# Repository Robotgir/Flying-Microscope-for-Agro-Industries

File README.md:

# Flying Microscope (SPECTORS)
This repo contains hardware and software details for the spore collector device which can be remotely controlled via Spectors Cockpit. Live image can be acessed on Spectors Cockpit.
## Code 
contains main script file named sporecollector1.py and its dependensies
### noteson_code.docx 
few details about the input variables in sporecollector1.py

## Docs 
contais system chart hand sketch  (Digital version yet to come)
### SystemChart.png coming soon
//

## Hardware
### camera_sieveholderassembly
contains priliminary and current designs for the spore collector device
### PCB (RPI HAT)
 contains Eagle board and schematic files for the PCB design
### productdata sheets
contain all the hardware components datasheets
#### PCB_connection_notes.docx 
contains details of how to setup the PCB AS Rpi-hat, connections with other components.

## Spore collection images
Images obtained from the measurment process

## PCB-Rpi-hat

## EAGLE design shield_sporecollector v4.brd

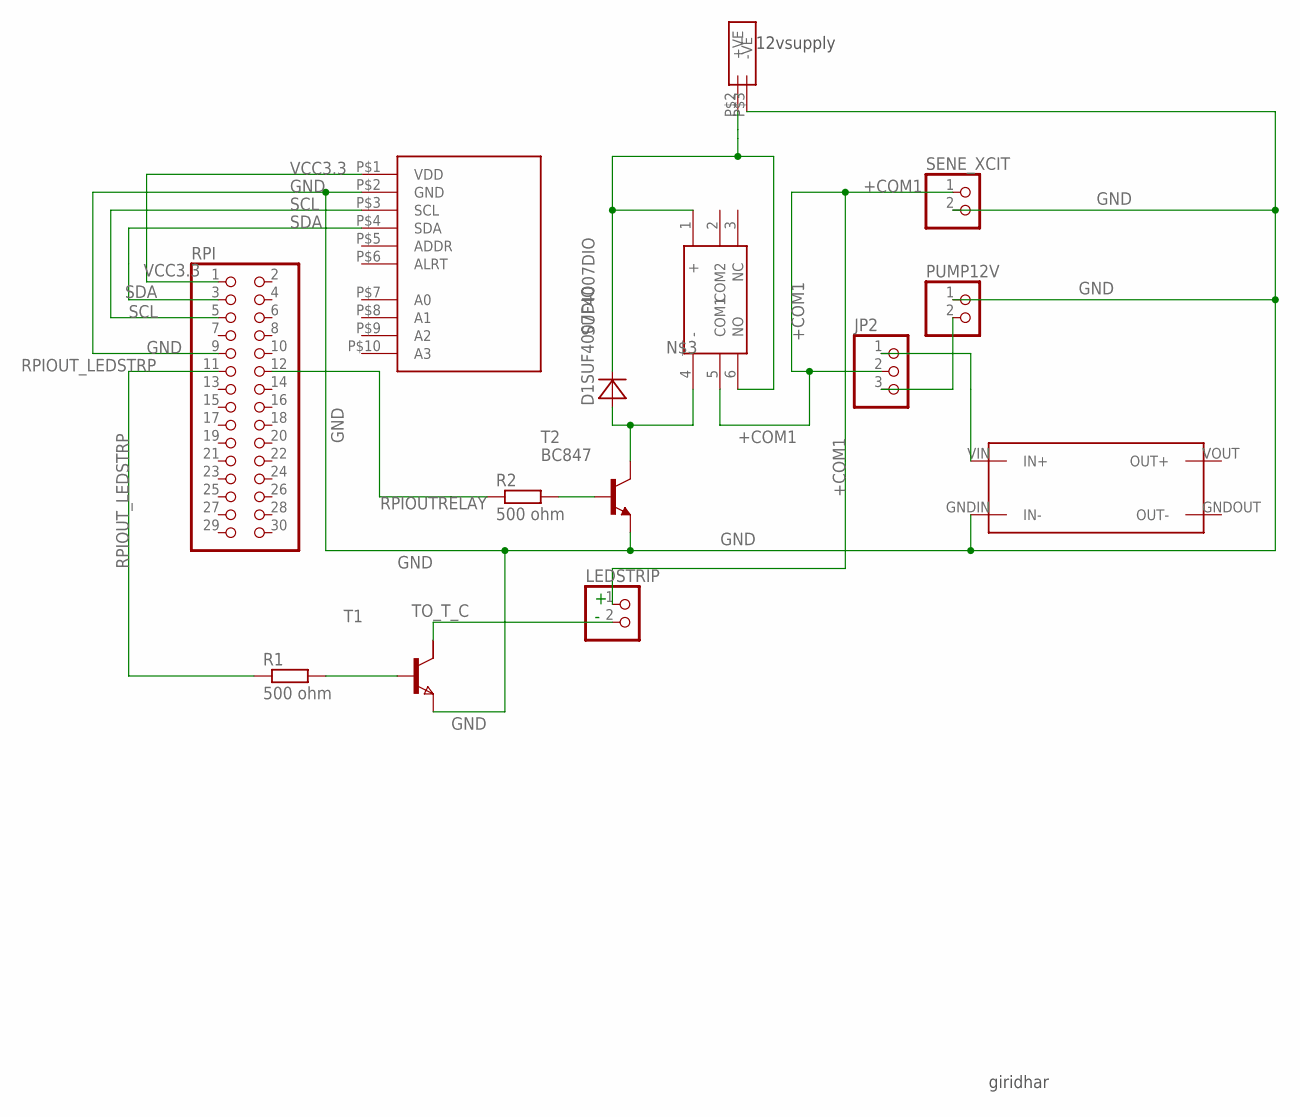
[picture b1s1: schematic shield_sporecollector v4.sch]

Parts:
BUCHSE12VINPUT: BUCHSE9.8X14.6
D1SUF4007DIO: SUF4007DIO; SUF4007
JP2: PINHD-1X3; 1X03
LEDSTRIP: PINHD-1X2; 1X02
PUMP12V: PINHD-1X2; 1X02
R1, R2: 500 ohm; R0603
RPI: PINHD-2X15; 2X15
SENE_XCIT: PINHD-1X2; 1X02
STEPUP12TO24V: 24VSTEPUPPOLOLUSMDSMD; STEP-UP24VSMD
T1: NPNSOT223; SOT223
T2: BC847; SOT23
U$3: ADC-4CH-ADS1115/WITHOUTHOLESADC-ADS1115WITHOUTHOL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; ADC-4CH-ADS1115/WITHOUTHOLES
U$4: G6B-2114POMRON; G6B-2114P

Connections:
+COM1: JP2.2, LEDSTRIP.1, SENE_XCIT.1, U$4.5 (COM1)
GND: BUCHSE12VINPUT.P$3 (-VE), PUMP12V.1, RPI.9, SENE_XCIT.2, STEPUP12TO24V.GNDIN (IN-), T1.3 (E), T2.2 (E), U$3.P$2 (GND)
unnamed: R2.2, T2.1 (B)
unnamed: R1.2, T1.1 (B)
unnamed: BUCHSE12VINPUT.P$2 (+VE), D1SUF4007DIO.C, U$4.1 (+), U$4.6 (NO)
unnamed: JP2.3, PUMP12V.2
unnamed: JP2.1, STEPUP12TO24V.VIN (IN+)
RELAY_T3_-_COIL: D1SUF4007DIO.A, T2.3 (C), U$4.4 (-)
RPIOUTRELAY: R2.1, RPI.12
RPIOUT_LEDSTRP: R1.1, RPI.11
SCL: RPI.5, U$3.P$3 (SCL)
SDA: RPI.3, U$3.P$4 (SDA)
TO_T_C: LEDSTRIP.2, T1.2 (C1)
VCC3.3: RPI.1, U$3.P$1 (VDD)

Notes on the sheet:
giridhar
12vsupply

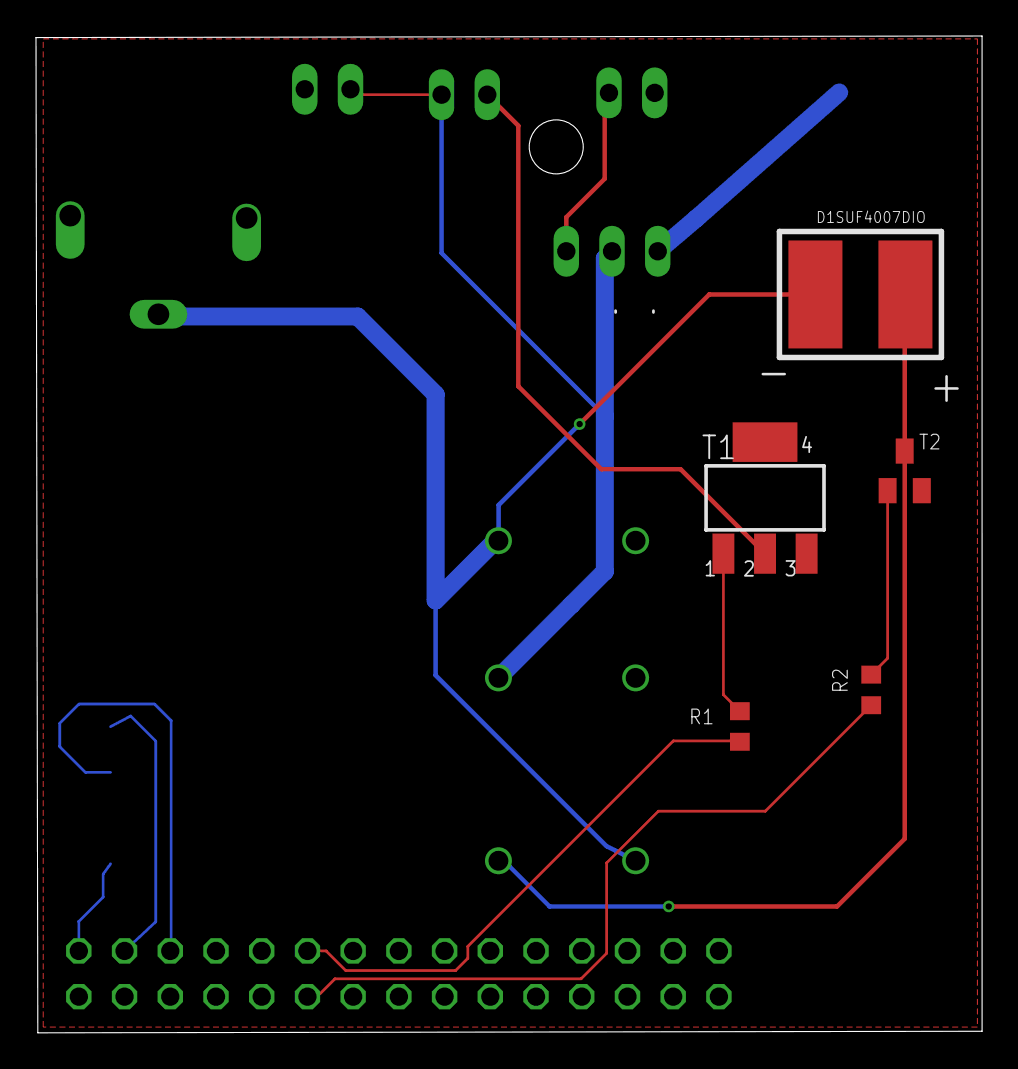
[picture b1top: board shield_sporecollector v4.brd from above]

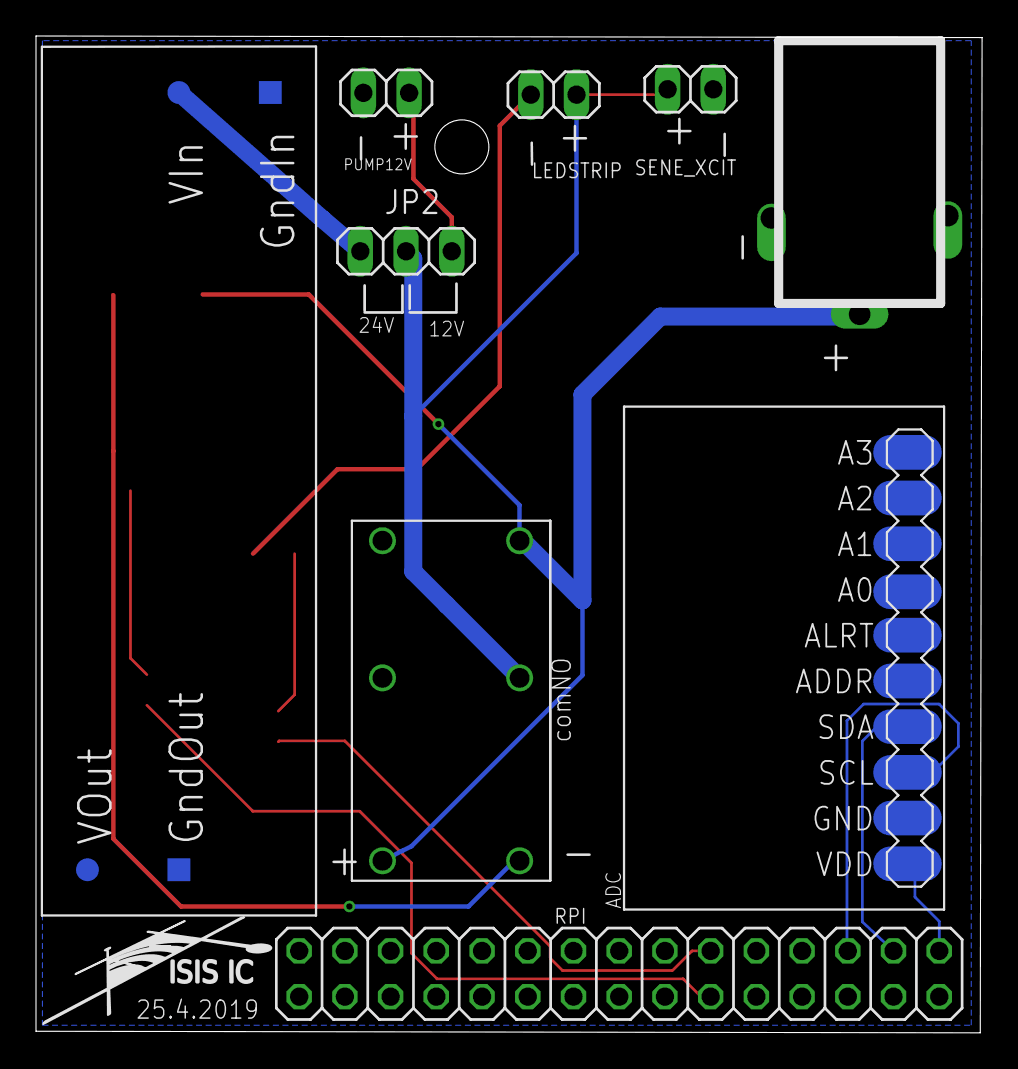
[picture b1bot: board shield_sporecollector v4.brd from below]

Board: 2 copper layers, 52.6 x 55.4 mm, 14 parts (9 on the bottom side), 14 nets.

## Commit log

2019-12-01 first update
2019-12-02 removed reports
2020-01-09 mage file_uploader to cloud
    image file_uploader to cloud
2020-01-10 info
2020-01-22 diffupload_method
2020-02-21 added python/bash scripts to upload the image and start/stop the measurement from the drone-cockpit
2020-02-21 added a handler for SIGTERM to the sporecollector-python script, so the measurement can be stopped correctly from the cockpit
2020-02-21 removed stdio output redirection
2020-02-21 added README.md
2020-04-29 organizing
2020-04-29 organized content
    readme update
2020-04-29 edit readme
2020-05-05 systemchart raw

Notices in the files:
parts and their libraries:
diy-modules: Released under the Creative Commons Attribution 4.0 International License: http://creativecommons.org/licenses/by/4.0
